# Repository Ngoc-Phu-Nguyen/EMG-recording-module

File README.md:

# EMG-recording-module
Design for the hardware of EMG recording module  and 3D with cases||
Code for system: STM8S, bluetooth HC-05, EMG recording module || 
# Hardware of EMG recording module
The module use a system filter that enough to clean the signal input before going to ADC. The ADC have I2C interface and programmable gain. The I2C is useful for multiple devices if necessary, and the programmable gain use for auto adjustment function.

Fig1. Scheme of circuit 

Fig2. 3D view of circuit

Fig3. 3D view with cases

Fig4. The real one - this module includes two main parts: Transmitter and receiver. The transmitter includes: STM8S, battery, EMG recording and HC-05. The receiver includes: black pill STM32, HC-05. 

Fig 5. Result of signal EMG from the module - Signal is quite clean. There is almost no noise and interference. The sampling rate of signal is 3ms.

# Coding
Using the tool ST Visual Develop to program and debug for STM8S: setup: CLK, peripheral - I2C, UART,...

Using Arduino and tool Arduino IDE to program for HC-05 (AT command)

Using tool STM32CubeIDE to program and debug for SMT32: peripheral UART

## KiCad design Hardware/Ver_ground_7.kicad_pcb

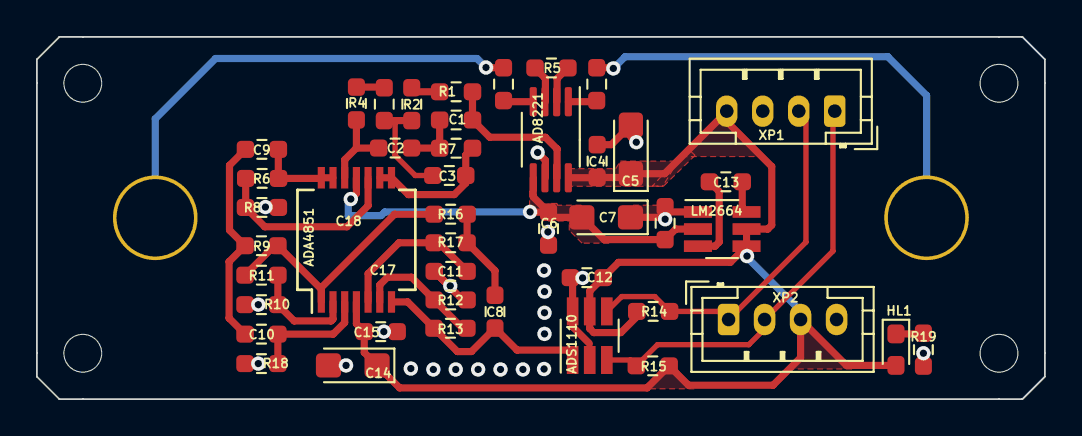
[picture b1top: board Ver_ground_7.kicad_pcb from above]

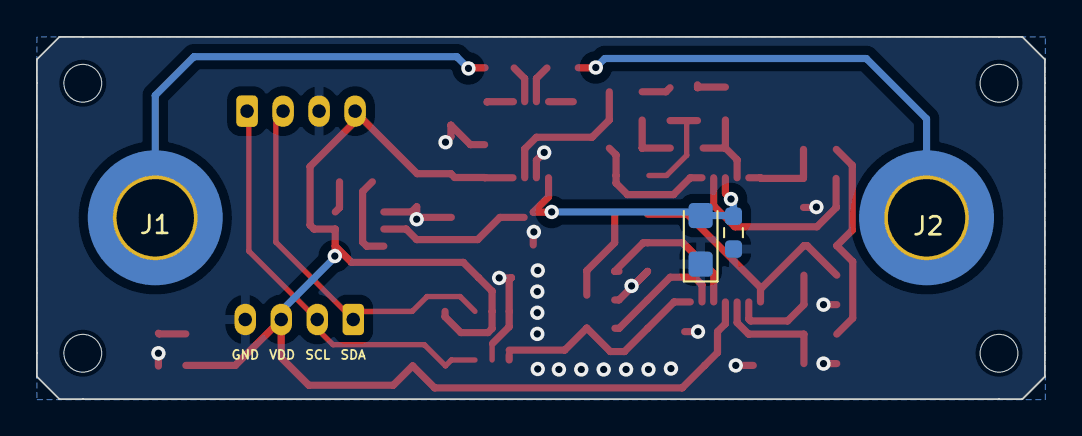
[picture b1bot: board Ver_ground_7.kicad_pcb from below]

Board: 2 copper layers, 56.0 x 20.1 mm, 52 parts (4 on the bottom side), 31 nets.

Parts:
C1, C2, C4, C6, C12: 0.1u; R_0603_1608Metric_Pad0.98x0.95mm_HandSolder
C3: 0.2u; R_0603_1608Metric_Pad0.98x0.95mm_HandSolder
C5, C7: 10u; CP_EIA-3216-18_Kemet-A
C8, C11: 3300p; R_0603_1608Metric_Pad0.98x0.95mm_HandSolder
C9, C10: 1u; R_0603_1608Metric_Pad0.98x0.95mm_HandSolder
C13, C16: 10u; R_0603_1608Metric_Pad0.98x0.95mm_HandSolder
C14, C17: 2.2u; CP_EIA-3216-18_Kemet-A
C15, C18: 0.01u; R_0603_1608Metric_Pad0.98x0.95mm_HandSolder
H1, H2, H3, H4: MountingHole; MountingHole_2.1mm
J1, J2: Conn_01x01_Pin; MountingHole_4.3mm_M4_DIN965_Pad_TopOnly
J3, J4: Conn_01x04_Pin; JST_PH_B4B-PH-K_1x04_P2.00mm_Vertical
LED1: IR26-21C_L110_TR8; LED_0603_1608Metric_Pad1.05x0.95mm_HandSolder
R1, R2, R3, R4, R7, R9, R18: 16k; R_0603_1608Metric_Pad0.98x0.95mm_HandSolder
R5, R6, R19: 1k; R_0603_1608Metric_Pad0.98x0.95mm_HandSolder
R8: 3.9k; R_0603_1608Metric_Pad0.98x0.95mm_HandSolder
R10, R12, R14, R15: 10k; R_0603_1608Metric_Pad0.98x0.95mm_HandSolder
R11, R13: 5.6k; R_0603_1608Metric_Pad0.98x0.95mm_HandSolder
R16, R17, R20, R21: 100k; R_0603_1608Metric_Pad0.98x0.95mm_HandSolder
U1: AD8221; MSOP-8_3x3mm_P0.65mm
U2: ADA4851; SSOP-14_5.3x6.2mm_P0.65mm
U3: LM2664; SOT-23-6_Handsoldering
U4: MCP3421; SOT-23-6_Handsoldering

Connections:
GNDA: C4.1, C5.2, C6.2, C7.1, C11.1, C12.1, C14.2, C15.1, C16.1, C17.1, C18.2, J3.3, J4.4, R8.1, R10.1, R12.2, R18.1, R19.1, U1.6 (Ref), U3.1 (GND), U4.2 (GND), U4.6 (VIN-)
unnamed: C1.1, R1.1, U1.7
unnamed: C1.2, C2.1, R7.2
unnamed: C3.2, R2.1, R3.2
unnamed: C8.2, R16.2, R17.1
unnamed: C9.2, C10.1, R9.1
unnamed: J1.1, R20.1
unnamed: J2.1, R21.1
unnamed: LED1.1 (K), R19.2
unnamed: R1.2, R2.2
unnamed: R3.1, R4.1
unnamed: R5.1, U1.2 (Rg)
unnamed: R5.2, U1.3 (Rg)
unnamed: R9.2, R11.2, R16.1, U2.1
unnamed: R21.2, U1.4 (+)
unnamed: R20.2, U1.1 (-)
unnamed: C10.2, R18.2, U2.3 (+)
unnamed: R10.2, R11.1, U2.2 (-)
unnamed: C11.2, R17.2, U2.5 (+)
unnamed: R12.1, R13.1, U2.6 (-)
unnamed: R6.1, R8.2, U2.10 (+)
unnamed: C3.1, R7.1, U2.8, U2.9 (-)
unnamed: C2.2, R4.2, U2.12 (+)
unnamed: C9.1, R6.2, U2.13 (-), U2.14
unnamed: C13.1, U3.6 (CAP+)
unnamed: C13.2, U3.3 (CAP-)
Out: C8.1, R13.2, U2.7, U4.1 (VIN+)
SCL: J3.1, J4.2, R15.1, U4.3 (SCL)
SDA: J3.2, J4.1, R14.1, U4.4 (SDA)
VDDA: C4.2, C5.1, C12.2, C14.1, C15.2, J3.4, J4.3, LED1.2 (A), R14.2, R15.2, U1.8 (Vs+), U2.4 (V+), U3.4 (nSD), U3.5 (V+), U4.5 (VDD)
VSSA: C6.1, C7.2, C16.2, C17.2, C18.1, U1.5 (Vs-), U2.11 (V-), U3.2 (OUT)

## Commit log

2024-04-21 commit change
2024-04-21 commit new file
2024-04-22 commit for gitignore
2024-04-22 commit for KidCad files
